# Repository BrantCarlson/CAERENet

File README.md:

CAERENet
========

Data processing, analysis, visualization, etc. for the Carthage Atmospheric Electricity Research and Education Network (CAERENet, see caerenet.org)

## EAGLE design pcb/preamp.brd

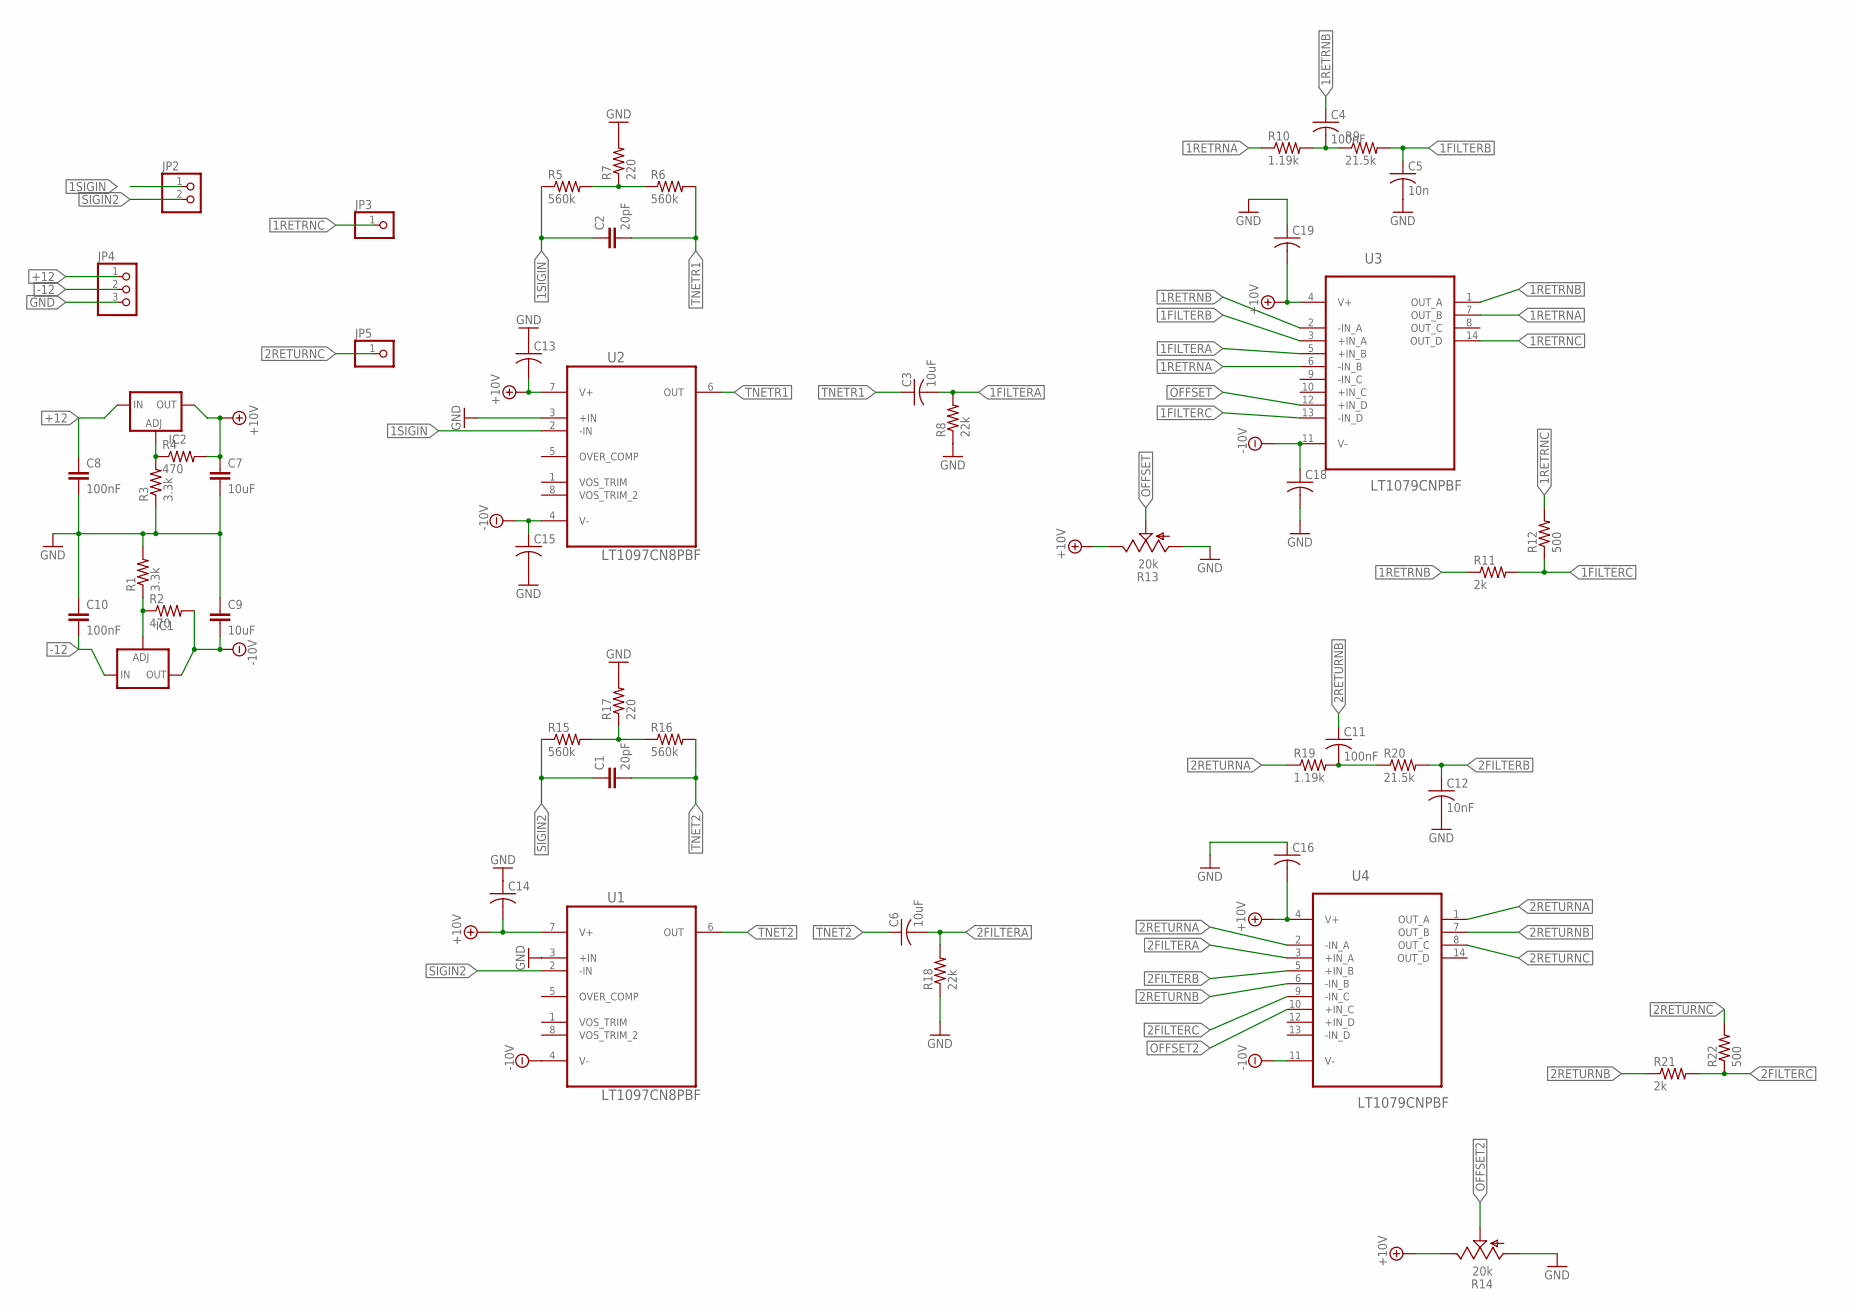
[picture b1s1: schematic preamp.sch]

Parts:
C1, C2: 20pF; C025-030X050
C3, C6: 10uF; C050-030X075
C4, C11: 100nF; C050-024X044
C5: 10n; C025-024X044
C7, C9: 10uF; C025-025X050
C8, C10: 100nF; C025-025X050
C12: 10nF; C025-024X044
C13, C14, C15, C16, C18, C19: C-US025-024X044; C025-024X044
IC1: LM337TS; 337TS
IC2: LM317TS; 317TS
JP2: PINHD-1X2; 1X02
JP3, JP5: PINHD-1X1; 1X01
JP4: PINHD-1X3; 1X03
R1, R3: 3.3k; 0204/5
R2, R4: 470; 0204/5
R5, R6, R15, R16: 560k; 0204/7
R7, R17: 220; 0204/7
R8, R18: 22k; 0204/5
R9, R20: 21.5k; 0204/5
R10, R19: 1.19k; 0204/5
R11, R21: 2k; 0204/5
R12, R22: 500; 0204/5
R13, R14: 20k; B64W
U1, U2: LT1097CN8PBF; DIP254P762X393-8
U3, U4: LT1079CNPBF; DIP254P762X394-14

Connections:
1FILTERA: C3.2, R8.2, U3.5 (+IN_B)
1FILTERB: C5.1, R9.2, U3.3 (+IN_A)
1FILTERC: R11.2, R12.1, U3.13 (-IN_D)
1RETRNA: R10.1, U3.6 (-IN_B), U3.7 (OUT_B)
1RETRNB: C4.1, R11.1, U3.1 (OUT_A), U3.2 (-IN_A)
1RETRNC: JP3.1, R12.2, U3.14 (OUT_D)
1SIGIN: C2.1, JP2.1, R5.1, U2.2 (-IN)
2FILTERA: C6.2, R18.2, U4.3 (+IN_A)
2FILTERB: C12.1, R20.2, U4.5 (+IN_B)
2FILTERC: R21.2, R22.1, U4.9 (-IN_C)
2RETURNA: R19.1, U4.1 (OUT_A), U4.2 (-IN_A)
2RETURNB: C11.1, R21.1, U4.6 (-IN_B), U4.7 (OUT_B)
2RETURNC: JP5.1, R22.2, U4.8 (OUT_C)
+10V: C7.1, C13.2, C14.2, C16.2, C19.2, IC2.2 (OUT), R4.2, R13.E, R14.E, U1.7 (V+), U2.7 (V+), U3.4 (V+), U4.4 (V+)
+12: C8.1, IC2.3 (IN), JP4.1
-10V: C9.2, C15.1, C18.1, IC1.3 (OUT), R2.2, U1.4 (V-), U2.4 (V-), U3.11 (V-), U4.11 (V-)
-12: C10.2, IC1.2 (IN), JP4.2
GND: C5.2, C7.2, C8.2, C9.1, C10.1, C12.2, C13.1, C14.1, C15.2, C16.1, C18.2, C19.1, JP4.3, R1.2, R3.1, R7.2, R8.1, R13.A, R14.A, R17.2, R18.1, U1.3 (+IN), U2.3 (+IN)
unnamed: IC2.1 (ADJ), R3.2, R4.1
unnamed: IC1.1 (ADJ), R1.1, R2.1
unnamed: R5.2, R6.1, R7.1
unnamed: C4.2, R9.1, R10.2
unnamed: R15.2, R16.1, R17.1
unnamed: C11.2, R19.2, R20.1
OFFSET: R13.S, U3.12 (+IN_D)
OFFSET2: R14.S, U4.10 (+IN_C)
SIGIN2: C1.1, JP2.2, R15.1, U1.2 (-IN)
TNET2: C1.2, C6.1, R16.2, U1.6 (OUT)
TNETR1: C2.2, C3.1, R6.2, U2.6 (OUT)

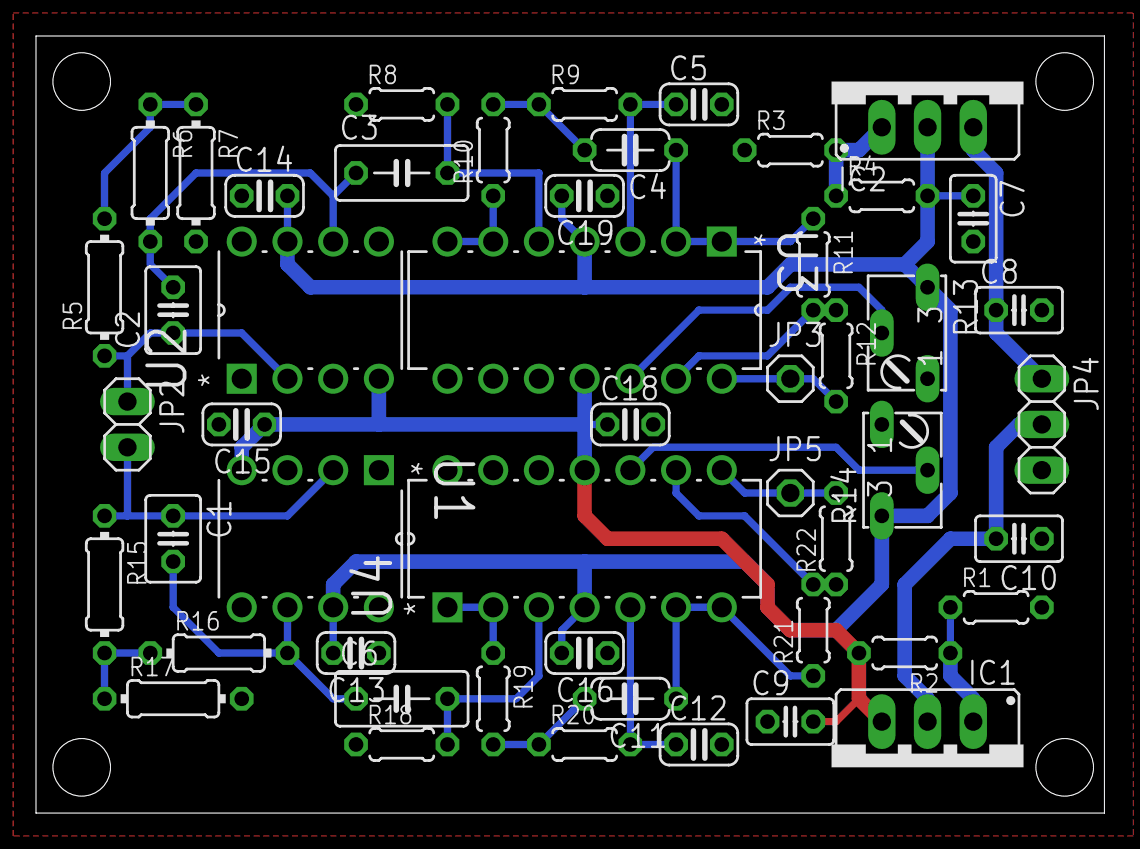
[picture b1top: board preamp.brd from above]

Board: 2 copper layers, 59.4 x 43.2 mm, 50 parts (0 on the bottom side), 29 nets.

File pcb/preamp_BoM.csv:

"Qty";"Value";"Device";"Package";"Parts";"Description";"MPN";"OC_FARNELL";"OC_NEWARK";"PACKAGE";"SUPPLIER";
"6";"";"C-US025-024X044";"C025-024X044";"C13, C14, C15, C16, C18, C19";"CAPACITOR, American symbol";"";"";"";"";"";
"1";"";"LM317TS";"317TS";"IC2";"VOLTAGE REGULATOR";"";"";"";"";"";
"1";"";"LM337TS";"337TS";"IC1";"VOLTAGE REGULATOR";"";"";"";"";"";
"2";"";"PINHD-1X1";"1X01";"JP3, JP5";"PIN HEADER";"";"";"";"";"";
"1";"";"PINHD-1X2";"1X02";"JP2";"PIN HEADER";"";"";"";"";"";
"1";"";"PINHD-1X3";"1X03";"JP4";"PIN HEADER";"";"";"";"";"";
"2";".015uF";"C-US050-024X044";"C050-024X044";"C4, C11";"CAPACITOR, American symbol";"";"";"";"";"";
"2";"1.6k";"R-US_0204/5";"0204/5";"R8, R18";"RESISTOR, American symbol";"";"";"";"";"";
"2";"100nF";"C-EU025-025X050";"C025-025X050";"C8, C10";"CAPACITOR, European symbol";"";"";"";"";"";
"2";"10uF";"C-EU025-025X050";"C025-025X050";"C7, C9";"CAPACITOR, European symbol";"";"";"";"";"";
"2";"10uF";"C-US050-030X075";"C050-030X075";"C3, C6";"CAPACITOR, American symbol";"";"";"";"";"";
"2";"16.2k";"R-US_0204/5";"0204/5";"R9, R20";"RESISTOR, American symbol";"";"";"";"";"";
"2";"20k";"TRIM_US-B64W";"B64W";"R13, R14";"POTENTIOMETER";"";"";"";"";"";
"2";"20pF";"C-EU025-030X050";"C025-030X050";"C1, C2";"CAPACITOR, European symbol";"";"";"";"";"";
"2";"220";"R-US_0204/7";"0204/7";"R7, R17";"RESISTOR, American symbol";"";"";"";"";"";
"2";"2k";"R-US_0204/5";"0204/5";"R11, R21";"RESISTOR, American symbol";"";"";"";"";"";
"2";"3.3k";"R-US_0204/5";"0204/5";"R1, R3";"RESISTOR, American symbol";"";"";"";"";"";
"2";"3300pF";"C-US025-024X044";"C025-024X044";"C5, C12";"CAPACITOR, American symbol";"";"";"";"";"";
"2";"470";"R-US_0204/5";"0204/5";"R2, R4";"RESISTOR, American symbol";"";"";"";"";"";
"2";"500";"R-US_0204/5";"0204/5";"R12, R22";"RESISTOR, American symbol";"";"";"";"";"";
"4";"560k";"R-US_0204/7";"0204/7";"R5, R6, R15, R16";"RESISTOR, American symbol";"";"";"";"";"";
"2";"7.9k";"R-US_0204/5";"0204/5";"R10, R19";"RESISTOR, American symbol";"";"";"";"";"";
"2";"LT1079CNPBF";"LT1079CNPBF";"DIP254P762X394-14";"U3, U4";"Precision Op Amps";"LT1079CN#PBF";"9559701";"57M1426";"PDIP-14";"Linear Technology";
"2";"LT1097CN8PBF";"LT1097CN8PBF";"DIP254P762X393-8";"U1, U2";"Precision Op Amp";"LT1097CN8#PBF";"9559914";"57M1574";"PDIP";"LINEAR TECHNOLOGY";

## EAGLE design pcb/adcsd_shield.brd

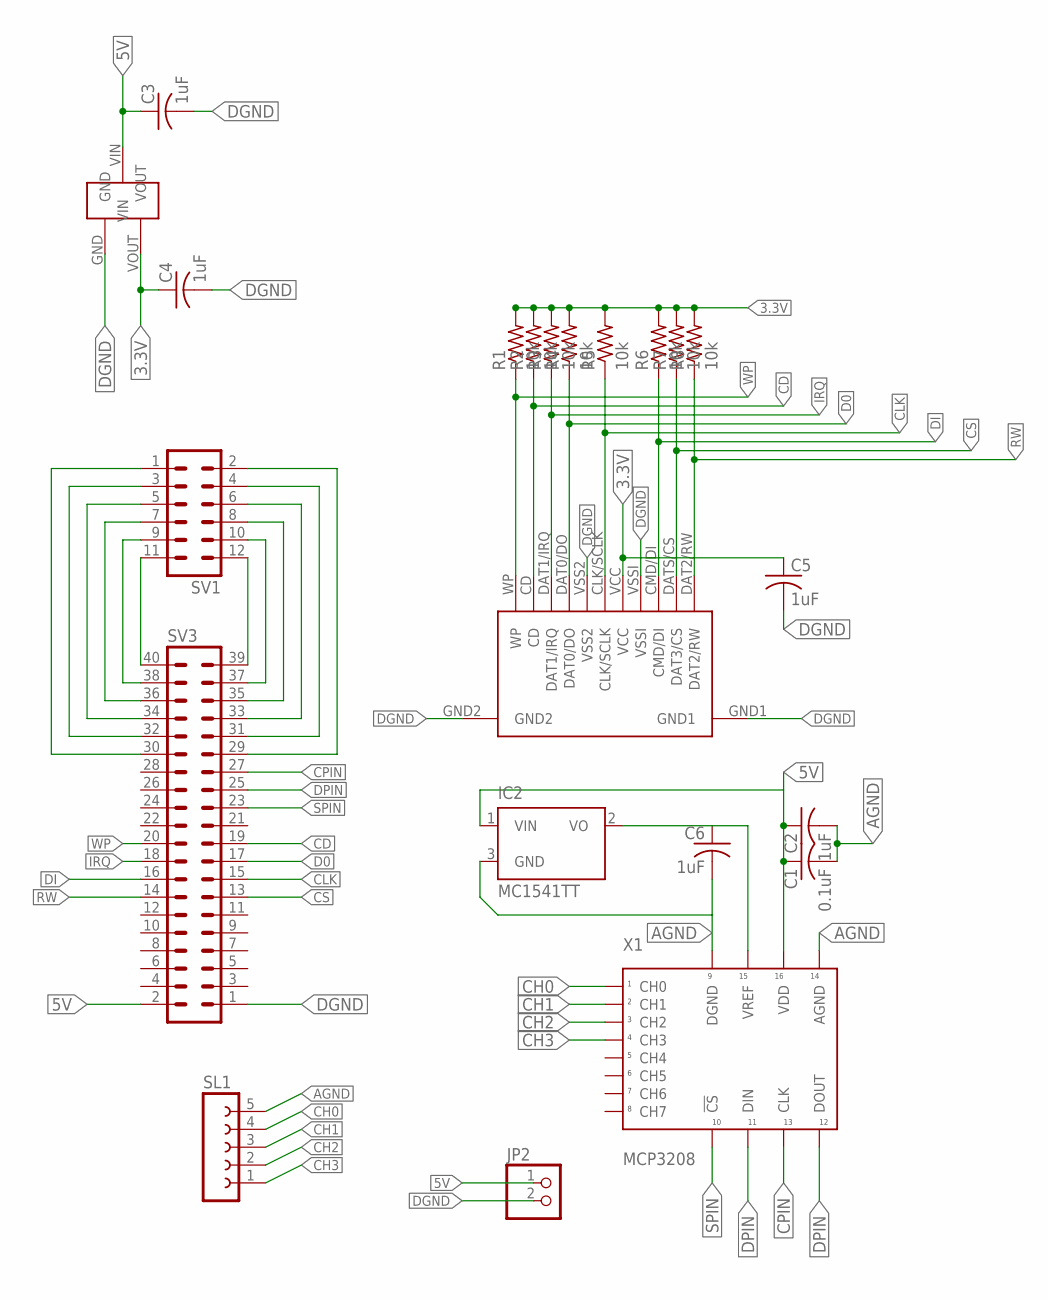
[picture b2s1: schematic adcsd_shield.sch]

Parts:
C1: 0.1uF; C0402
C2, C3, C4, C5, C6: 1uF; C0402
IC2: MC1541TT; SOT23
JP2: PINHD-1X2; 1X02
R1, R2, R3, R4, R5, R6, R7, R8: 10k; R0603
SL1: FE05-1
SV1: MA06-2
SV3: MA20-2
U$1: SD_1.0
U$2: MCP1700T; SOT23
X1: MCP3208; DIP16

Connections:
3.3V: C4.1, C5.1, R1.2, R2.2, R3.2, R4.2, R5.2, R6.2, R7.2, R8.2, U$1.VCC, U$2.VOUT
5V: C1.1, C2.1, C3.1, IC2.1 (VIN), JP2.1, SV3.2, U$2.VIN, X1.P$16 (VDD)
AGND: C1.2, C2.2, C6.2, IC2.3 (GND), SL1.5, X1.P$9 (DGND), X1.P$14 (AGND)
CD: R2.1, SV3.19, U$1.CD
CH0: SL1.4, X1.P$1 (CH0)
CH1: SL1.3, X1.P$2 (CH1)
CH2: SL1.2, X1.P$3 (CH2)
CH3: SL1.1, X1.P$4 (CH3)
CLK: R5.1, SV3.15, U$1.CLK/SCLK
CPIN: SV3.27, X1.P$13 (CLK)
CS: R7.1, SV3.13, U$1.DATS/CS (DAT3/CS)
D0: R4.1, SV3.17, U$1.DAT0/DO
DGND: C3.2, C4.2, C5.2, JP2.2, SV3.1, U$1.GND1, U$1.GND2, U$1.VSS2, U$1.VSSI, U$2.GND
DI: R6.1, SV3.16, U$1.CMD/DI
DPIN: SV3.25, X1.P$11 (DIN), X1.P$12 (DOUT)
IRQ: R3.1, SV3.18, U$1.DAT1/IRQ
unnamed: SV1.1, SV3.30
unnamed: SV1.3, SV3.32
unnamed: SV1.5, SV3.34
unnamed: SV1.2, SV3.29
unnamed: SV1.4, SV3.31
unnamed: SV1.6, SV3.33
unnamed: SV1.7, SV3.36
unnamed: SV1.9, SV3.38
unnamed: C6.1, IC2.2 (VO), X1.P$15 (VREF)
unnamed: SV1.11, SV3.40
unnamed: SV1.8, SV3.35
unnamed: SV1.10, SV3.37
unnamed: SV1.12, SV3.39
RW: R8.1, SV3.14, U$1.DAT2/RW
SPIN: SV3.23, X1.P$10 (!CS)
WP: R1.1, SV3.20, U$1.WP

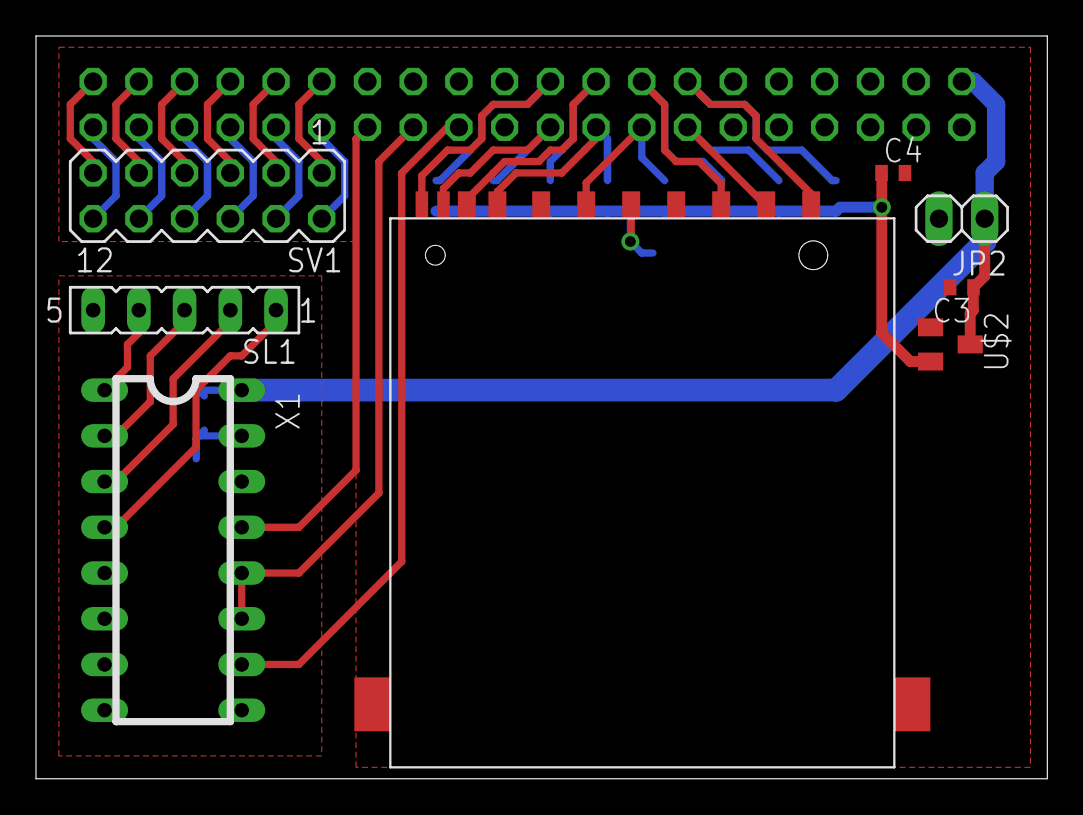
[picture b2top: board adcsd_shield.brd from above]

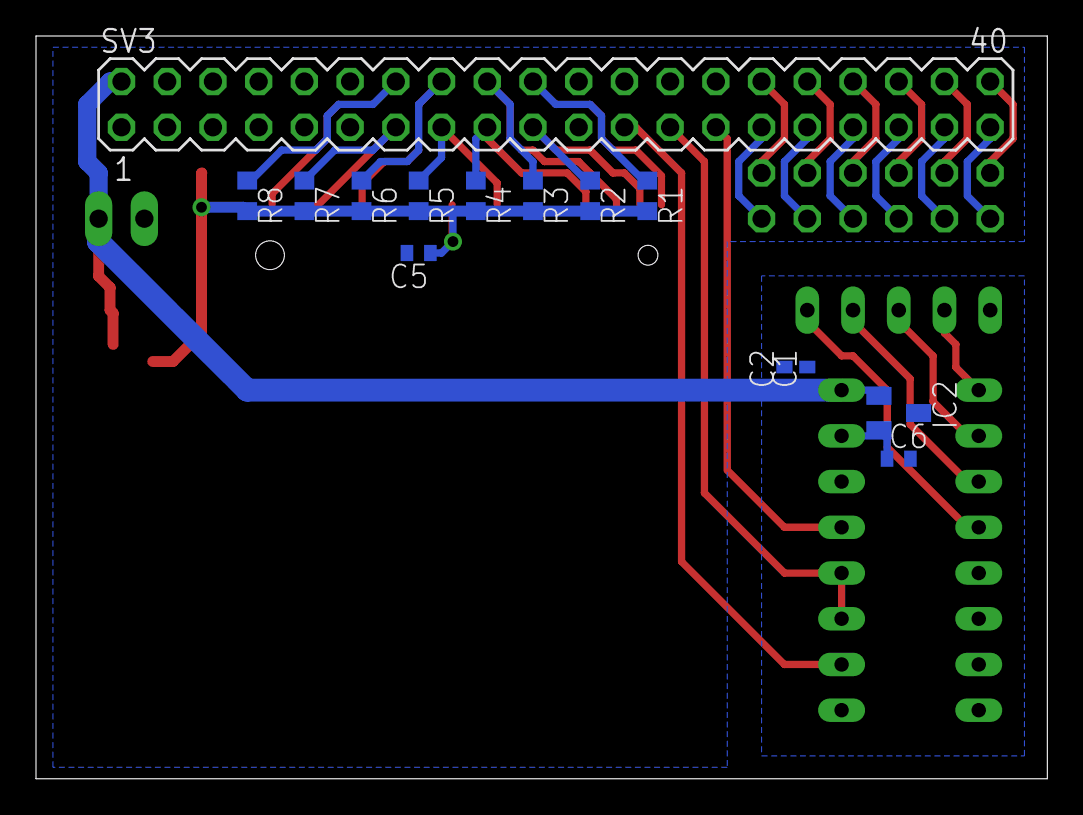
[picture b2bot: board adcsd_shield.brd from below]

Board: 2 copper layers, 56.2 x 41.3 mm, 22 parts (14 on the bottom side), 32 nets.

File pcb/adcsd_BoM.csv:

"Qty";"Value";"Device";"Package";"Parts";"Description";"MF";"MPN";"OC_FARNELL";"OC_NEWARK";
"1";"";"FE05-1";"FE05-1";"SL1";"FEMALE HEADER";"";"";"unknown";"unknown";
"1";"";"MA06-2";"MA06-2";"SV1";"PIN HEADER";"";"";"unknown";"unknown";
"1";"";"MA20-2";"MA20-2";"SV3";"PIN HEADER";"";"";"unknown";"unknown";
"1";"";"PINHD-1X2";"1X02";"JP2";"PIN HEADER";"";"";"";"";
"1";"0.1uF";"C-USC0402";"C0402";"C1";"CAPACITOR, American symbol";"";"";"";"";
"8";"10k";"R-US_R0603";"R0603";"R1, R2, R3, R4, R5, R6, R7, R8";"RESISTOR, American symbol";"";"";"";"";
"5";"1uF";"C-USC0402";"C0402";"C2, C3, C4, C5, C6";"CAPACITOR, American symbol";"";"";"";"";
"1";"MC1541TT";"MC1541TT";"SOT23";"IC2";"2.5V and 4.096V Voltage References";"";"";"unknown";"unknown";
"1";"MCP1700T";"MCP1700T";"SOT23";"U$2";"";"";"";"";"";
"1";"MCP3208";"21298EDIP";"DIP16";"X1";"";"";"";"";"";
"1";"SD_1.0";"SD_1.0";"SD_1.0";"U$1";"";"";"";"";"";

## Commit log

2014-06-01 fixing a spelling error (urgh)
2014-06-01 adding initial drafts (unedited) from summer 2013
    ... and related work from fall 2013.
    note also .gitignore file to ignore .pyc files
2014-06-01 adding configuration file
2014-06-01 creating examples.ipynb and findEField.py
    a bit more friendly than the old notebooks.
2014-06-01 data location added
2014-06-10 adding spectrogram, power spectrum plotting code
2014-07-30 reorganizing and getting things uploaded to git
2014-07-30 deleted waitcnt test
2014-07-30 no major changes
2014-08-01 yeah, whatever
2014-08-02 adding spin code on propeller
2014-08-02 reorganizing
2014-08-02 reorganization again
2014-08-03 adding old version, support libraries
2014-08-03 cleaning up spin code
    note: uncompiled, untested
2014-08-03 cleanup python on RPi
    note: untested
2014-08-09 required for fsrw
2014-08-09 fixing formatting, adding Makefile
    for use on linux with simpleIDE (for propeller-load) and the Brad's Spin
    Tool compiler (bstc.linux). YMMV -- check the paths in the Makefile.
2014-08-12 adding some C GPIO test code with wiringPi
2014-08-12 changing delay, fixing makefile
    test C GPIO code with wiringpi works...
    now to edit it to handle the pesudo-SPI...
2014-08-12 adding pseudoSPI draft (probably buggy)
    untested
2014-08-13 adding io16 function, editing io1 a bit
2014-08-14 adding ADC/SD shield board and schematic to repo
2014-08-14 adding preamp schematic and board layout to repo
2014-08-14 adding notes or electronics
2014-08-14 adding ADC pinout document
2014-08-14 adding FSRW test code for ADC/SD shield
    will move to own directory later
2014-08-14 moving fsrw_test to own directory
2014-08-14 adding files needed for fsrw_test, editing makefile
    everything works now...
    note: pst.str(string(13,10)) sends CRLF for compatibility with xterm.
    string(13) suffices with the parallax serial terminal, but that is
    evidentyl non-standard? see
    http://forums.parallax.com/archive/index.php/t-150741.html for more
    info/ranting.
2014-08-14 testing MCP3208, fixing pinout
    works fine
2014-08-14 fixing pin numbers for main program
2014-08-15 adding pseudoSPI_test code
    haven't tested it yet, though.
2014-08-15 adding no-output speed test
2014-08-15 adding necessary files
2014-08-15 adding speed test wiringPi code
2014-08-15 adding python speed test, fixing pins in main code
2014-08-15 documenting speed test results
    see comments in pseudoSPI_speedtest.spin.
    the punchline: python on RPi isn't that much slower than C/wiringPi.
    I'm surprised.
2014-08-15 final speed tests in python
2014-08-15 make clean doesn't need to recurse...
2014-08-15 adding comments re: pinout
2014-08-15 ...duh, have to call the main function...
2014-08-19 some new files, also converting to utf8
2014-08-19 probably just messed everything up
    converting from utf16 to utf8
2014-08-19 more format changes
    everthing should be utf-8 with unix line-endings now.
2014-08-19 renaming to keep with other conventions
2015-01-01 starting simple no-daq version
2015-01-01 stripping down prop.spin for no-daq code.
2015-01-01 adjusting to 10s of run-time before shutdown
2015-01-03 some issues discovered but not fixed...
    clk will nto fit in a "word", but "word" is the data type used for the
    buffer. I'm overflowing and losing time info.
2015-01-03 no-communications data collection
    seems to work with ADC/SD shield... be sure SD shield ADC part has
    proper ground.
    I also fried and ADC chip somehow in there.. not sure how.
2015-01-23 adding tentative pinout
2015-03-15 test commit, minor changes to a .ipynb file?
2015-07-07 updating things
    note repo is now in "git" directory, not "code".
2015-07-07 adding part drawings and 3d print files
2015-07-07 starting to work out wiring details
2015-07-07 updated todo lists
2015-07-08 moving documentation around
2015-07-08 adding a bit of paranoia Re: ESC BEC power
2015-07-08 adding docs, starting more wiring documentation
2015-07-09 adding initial prototype design for esc holder, some updated docs
2015-07-09 photogate mount slots go all the way to the edge now.
2015-07-09 adding motor guard designs
2015-07-09 updated wiring docs, adding some straggler files
2015-07-09 incorporated into other docs
2015-07-09 adding photogate power to pinout
2015-07-09 adding photogate signal designation to pinout image
2015-07-09 cleaning up readme
2015-07-09 adding ideas Re: grounding
2015-07-14 some updates
2015-07-17 working. sigh...
    propeller-load comes from simpleide
    you don't need the entire package, just the parts that deal with
    propeller-load, so... extract the .deb file (dpkg -x something.deb) and
    just call the propeller-load executable from whatever directory.
2015-07-17 about to test?
2015-07-17 ok, looks to be working, but ... no dice on the ESC.
    needs more power... will have to look into other power supplies.
2015-07-17 random testing, no real changes.
2015-07-20 adding notes on how to deal with power supply issues
    also updating motor guard designs to be stronger
2015-07-20 moar data
2015-07-20 utility to help with ESC calibration
2015-07-20 adding notes Re: ESC calibration
2015-07-20 copy of examples for scratch work
    for the most part, ignore changes to this file.
2015-07-21 attempted fix of long cnt --> word buffer_1[0] issue
    probably doesn't work, needs to be checked.
2015-07-21 adding code to properly incement filenames
    from
    http://forums.parallax.com/discussion/106345/can-the-propeller-support-string-variables-or-other-useful-string-operations
    September 8th 2008 post by Mike Green
    compiles, but untested.
2015-07-21 it works. time for some serious tests.
2015-07-21 starting noise tests
2015-07-22 updating docs
2015-07-22 fixed overrun in data read code
    working on noise analysis
2015-07-22 noise analysis done. now, to fix things...
2015-07-23 bulk of noise is coming from power supply coupling
2015-07-24 updated noise analysis, going for long data collection
2015-07-28 more noise debugging, some simulating
2015-07-28 some circuit modifications, updates
2015-07-29 playing with simulation, updating component values accordingly
    decreasing distortion
    component values in the simulation are now more correct.
2015-07-29 updating schematic to reflect new component values
2015-07-31 playing with data, designing box mount
    seems to print a bit too small.
2015-07-31 increasing size of openings for nut in boxmount
2015-07-31 increasing size of bolt hole to accomodate screw head
2015-07-31 back to 48hours of data taking
2015-07-31 increasing size of box mount to better stabilize box
    started mucking aroud with julia
2015-08-03 working on julia stuff, bigger box gcode
2015-08-03 julia data processing now works
2015-08-03 adding notes on data processing
    should update this later
